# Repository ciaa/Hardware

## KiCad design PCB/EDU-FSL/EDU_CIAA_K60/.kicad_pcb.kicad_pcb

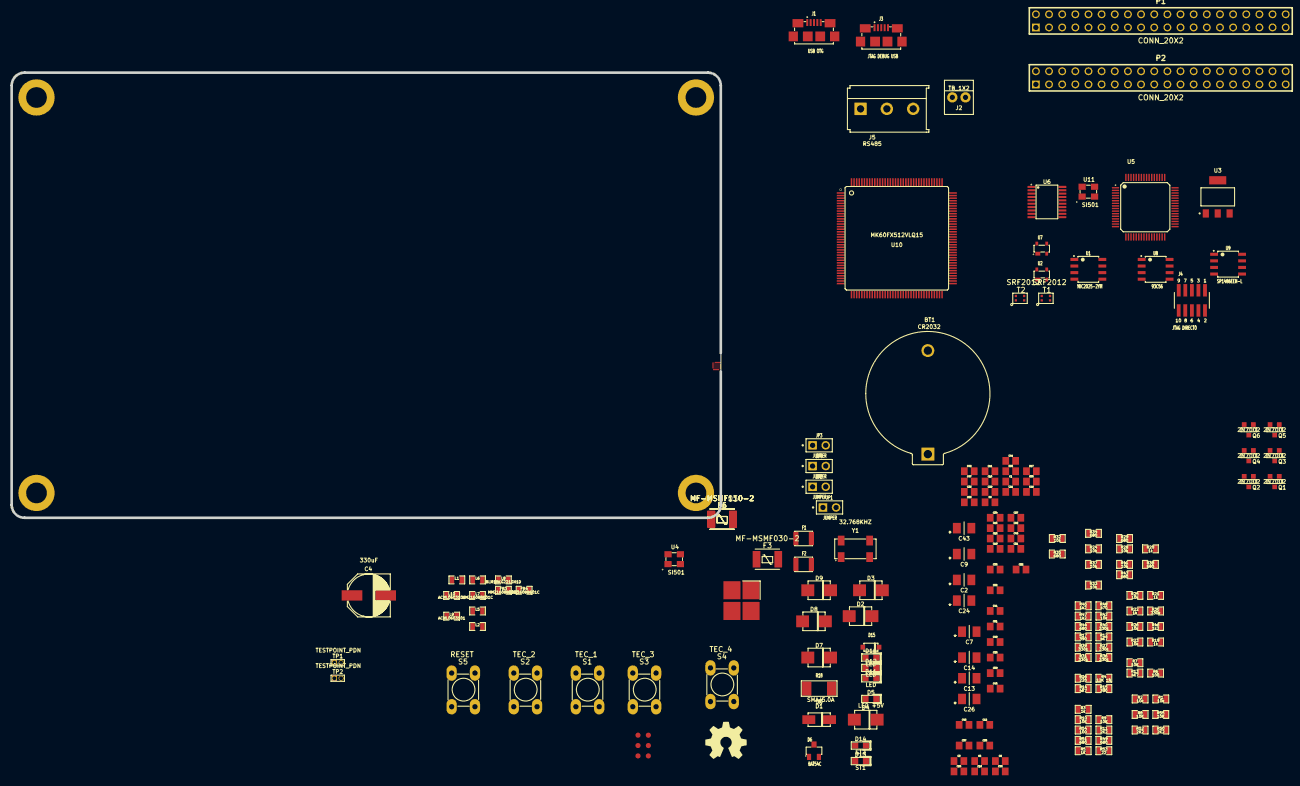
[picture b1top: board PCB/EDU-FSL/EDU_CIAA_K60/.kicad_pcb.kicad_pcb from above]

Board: 2 copper layers, 137.0 x 86.0 mm, 188 parts (0 on the bottom side), 164 nets, no tracks yet.

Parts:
BT1: CR2032; 2032batPTH
C1, C3, C5, C6, C8, C10, C11, C12, C15, C16, C17, C18, C19, C20, C21, C22, C23, C25, C27, C28, C29, C30, C31, C33, C34, C35, C37, C38, C39, C40, C41, C42, C44, C45, C48, C49, C50: 100nF; c_0805
C2, C9, C13, C14, C24: 4,7uF; c_1206POL
C4: 330uF; c_elec_8x10
C7, C26, C43: 10uF; c_1206POL
C32, C36: 18pF; c_0805
C46: 2.2uF; c_0805
C47, C51: 10nF; c_0805
D1: SMAJ5.0A; DO-214AC_SMA
D2, D3, D4: MBRS130LT3G; DO-214AA_SMB
D5: LED +5V; LED-0805
D6: BAT54C; SOT-23
D7, D8, D9: P6SMB12CAT3G; DO-214AA_SMB
D10, D11, D12: LED; LED-0805
D13: ST1; LED-0805
D14: ST2; LED-0805
D15: LL4148; SOD-123
F1, F2: USMF020; ptc_1210
F3, F5: MF-MSMF030-2; MF-MSMF
F4, F6: MF-MSMF110-2; MF-MSMF
FB3, FB4: MMZ1608B601C; SM0805
FD1, FD2, FD3, FD4, FD5, FD6: FIDUCIAL; Fiducial_1mm
G2: OSHWA
J1: USB OTG; USB_MicroAB
J2: TB_1X2; Con_2P
J3: JTAG DEBUG USB; USB_MicroAB
J4: JTAG DIRECTO; PIN_ARRAY_5x2_1.27_SMD
J5: RS485; bornier3
JP1, JP2, JP3, JP4: JUMPER; PIN_ARRAY_2x1
L1, L2, L5, L6: SM0805
L7: MMZ1608B601C; SM0805
L8: BLM18KG221SN1D; SM0805
L9, L10: ACML0603101; SM0805
LED1: LED_ARBG; PLCC-4
MH1, MH2, MH3, MH4: PCB_HOLE
P1, P2: CONN_20X2; PIN_ARRAY_20X2
Q1, Q2, Q3, Q4, Q5, Q6: 2N7002; SOT23GDS
R1, R2: 10k; r_0805
R3: 1k; r_0805
R4: 12K 1%; r_0805
R5: 1K; r_0805
R6, R54: 100; r_0805
R7, R8, R9, R10, R55: 10K; r_0805
R11, R50, R52: 2K2; r_0805
R12, R13, R14: 4K7; r_0805
R15, R17: 390; r_0805
R16: 220; r_0805
R18: 100; r_2010
R19, R20, R21, R22: 1k; SM0805
R23, R24, R25, R26, R28, R32, R33, R37, R41, R42: 10k; SM0805
R27, R30, R31, R36, R39, R40: 330k; SM0805
R29, R34, R35, R38, R43, R44: 680; SM0805
R45, R46, R47: 1k2; SM0805
R48: 470; SM0805
R49, R51: 680; r_0805
R53: 22; r_0805
S1: TEC_1; PUSH_SWITCH_THT
S2: TEC_2; PUSH_SWITCH_THT
S3: TEC_3; PUSH_SWITCH_THT
S4: TEC_4; PUSH_SWITCH_THT
S5: RESET; PUSH_SWITCH_THT
T1, T2: SRF2012
TP1, TP2: TESTPOINT_PDN
U1: MIC2025-2YM; SOIC-8
U2, U7: PRTR5V0U2X; SOT-143-4
U3: NCP1117ST33T3G; SOT-223
U4, U11: SI501; SI501_C
U5: FT2232H; TQFP64
U6: 74HC244; TSSOP-20
U8: 93C56; SOIC-8
U9: SP1486EEN-L; SOIC-8
U10: MK60FX512VLQ15; LQFP144
Y1: 32.768KHZ; 4SOJ

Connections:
+3.3V: C7.1, C8.1, C18.1, C19.1, C20.1, C21.1, C22.1, C23.1, C33.1, C34.1, C35.1, C37.1, C38.1, C39.1, C40.1, C41.1, C42.1, C43.1, C49.1, D6.2, F3.2, F5.2, FB3.1, J4.1, L5.1, L6.1, R2.1, R5.1, R7.2, R8.1, R9.1, R10.1, R23.1, R24.1, R25.1, R26.1, R50.1, R52.1, R55.1, TP1.1, U3.2, U4.1, U4.4, U5.20, U5.31, U5.42, U5.50, U5.56, U6.20, U8.6, U8.8, U10.5, U10.16, U10.43, U10.56, U10.70, U10.94, U10.108, U10.122, U10.135, U11.1, U11.4
+3.3VADC: C50.1, C51.2, FB3.2, L9.2, P1.15, U10.31
+5V: C1.1, C4.1, C5.1, C26.1, C27.2, D2.2, D3.2, D4.2, D10.1, D11.1, D12.1, F4.2, F6.2, LED1.4, R3.1, R13.1, R15.1, TP2.1, U1.7, U3.3, U9.8
+USB_JTAG_1V8: C9.1, C10.1, C15.1, C16.1, C17.1, U5.12, U5.37, U5.49, U5.64
/CPU/AUX_UART_CTS/SPI_CLK: P2.20, U10.128
/CPU/AUX_UART_RTS/SPI_CS: P2.22, U10.127
/CPU/AUX_UART_RX/SPI_MISO: P2.18, U10.130
/CPU/AUX_UART_TX/SPI_MOSI: P2.21, U10.129
/CPU/CAN_RD: P1.27, U10.98
/CPU/CAN_STB: P1.28, U10.54
/CPU/CAN_TD: P1.29, U10.97
/CPU/ETH_RST: P2.13, U10.73
/CPU/ETH_RXER: P2.11, U10.55
/CPU/I2C_SCL: P1.19, R52.2, U10.137
/CPU/I2C_SDA: P1.17, R50.2, U10.138
/CPU/LED0_B: R27.1, R28.1, U10.111
/CPU/LED0_G: R30.1, R32.1, U10.110
/CPU/LED0_R: R36.1, R37.1, U10.109
/CPU/LED1: R39.1, R41.1, U10.112
/CPU/LED2: R31.1, R33.1, U10.113
/CPU/LED3: R40.1, R42.1, U10.114
/CPU/PULS_0: R19.1, U10.103
/CPU/PULS_1: R20.1, U10.104
/CPU/PULS_2: R21.1, U10.105
/CPU/PULS_3: R22.1, U10.106
/CPU/RESET: D15.2, J4.10, P1.3, U6.12
/CPU/RS232_CTS: P1.22, U10.90
/CPU/RS232_RTS: P1.23, U10.89
/CPU/RS232_RXD: P1.21, U10.91
/CPU/RS232_TXD: P1.25, U10.92
/CPU/RS485_DIR: JP1.2, R14.2, U9.3, U10.131
/CPU/RS485_RXD: R13.2, U9.1, U10.133
/CPU/RS485_TXD: U9.4, U10.136
/CPU/SD_CLK: P2.35, R53.2
/CPU/SD_CMD: P2.36, U10.4
/CPU/SD_DAT0: P2.31, U10.2
/CPU/SD_DAT1: P2.38, U10.1
/CPU/SD_DAT2: P2.33, U10.8
/CPU/SD_DAT3: P2.40, U10.7
/CPU/SD_POW: P2.29, U10.126
/CPU/TCK: J4.4, U6.18, U10.50
/CPU/TDI: J4.8, U6.16, U10.51
/CPU/TDO: J4.6, U6.15, U10.52
/CPU/TEC_COL0: P1.39, U10.115
/CPU/TEC_COL1: P1.31, U10.116
/CPU/TEC_COL2: P1.34, U10.117
/CPU/TEC_F0: P1.33, U10.60
/CPU/TEC_F1: P1.36, U10.61
/CPU/TEC_F2: P1.37, U10.62
/CPU/TEC_F3: P1.35, U10.63
/CPU/TMS: J4.2, U6.14, U10.53
/CPU/USB_DM: T1.3, U2.2, U10.20
/CPU/USB_DP: T1.2, U2.3, U10.19
/CPU/USB_ID: D1.2, J1.4, U10.123
/CPU/USB_JTAG_UART_RXD: U5.38, U10.12
/CPU/USB_JTAG_UART_TXD: U5.39, U10.11
/CPU/VBAT: C6.1, D6.3, U10.42
/CPU/VREFH: C45.1, C47.2, L9.1, U10.32
/CPU/VREFL: C44.2, C45.2, C47.1, L10.1, U10.33
/Fuente/USB_VBUS: C2.1, C3.1, D3.1, L1.1, U1.6, U1.8, U2.4, U10.22
/GPIO/ADC0_1: R47.1, U10.77
/GPIO/ADC0_2: R46.1, U10.78
/GPIO/ADC0_3: R45.1, U10.79
/GPIO/DAC: R48.1, U10.38
/GPIO/ENET_CRS_DV: P2.10, U10.66
/GPIO/ENET_MDC: P2.8, U10.82
/GPIO/ENET_MDIO: P2.12, U10.81
/GPIO/ENET_REF_CLK: P2.15, U10.72
/GPIO/ENET_RXD0: P2.9, U10.65
/GPIO/ENET_RXD1: P2.4, U10.64
/GPIO/ENET_TXD0: P2.14, U10.68
/GPIO/ENET_TXD1: P2.16, U10.69
/GPIO/ENET_TX_EN: P2.6, U10.67
/GPIO/LCD1: P2.34, U10.141
/GPIO/LCD2: P2.32, U10.142
/GPIO/LCD3: P2.30, U10.143
/GPIO/LCD4: P2.26, U10.144
/GPIO/LCD_EN: P2.24, U10.139
/GPIO/LCD_RS: P2.28, U10.140
/JTAG/CHS_DBG: J3.6, J3.7, J3.8, J3.9, L7.2, U7.1
/JTAG/EECLK: R9.2, U5.62, U8.2
/JTAG/EECS: R8.2, U5.63, U8.1
/JTAG/EEDATA: R11.1, U5.61, U8.3
/JTAG/FT_OE: R7.1, U5.28, U6.1
/JTAG/FT_RST: U5.27, U6.8
/JTAG/FT_TCK: U5.16, U6.2
/JTAG/FT_TDI: U5.17, U6.4
/JTAG/FT_TDO: U5.18, U6.5
/JTAG/FT_TMS: U5.19, U6.6
/JTAG/USB_DEBUG_VBUS: C24.1, C25.1, D4.1, L8.2
/JTAG/USB_JTAG_DM: T2.3, U5.7, U7.3
/JTAG/USB_JTAG_DP: T2.2, U5.8, U7.2
/USB OTG/CHS_OTG: D1.1, J1.6, J1.7, J1.8, J1.9, L2.2, U2.1
/USB OTG/USB0_PPWR: R1.2, U1.1, U10.125
/USB OTG/USB0_PWR_FAULT: R2.2, U1.2, U10.124
/USB OTG/USB_DM_OTG: J1.2, T1.4
/USB OTG/USB_DP_OTG: J1.3, T1.1
GND: BT1.2, C1.2, C2.2, C3.2, C4.2, C5.2, C6.2, C7.2, C8.2, C9.2, C10.2, C11.2, C12.2, C13.2, C14.2, C15.2, C16.2, C17.2, C18.2, C19.2, C20.2, C21.2, C22.2, C23.2, C24.2, C25.2, C26.2, C27.1, C28.2, C29.2, C30.2, C31.2, C32.2, C33.2, C34.2, C35.2, C36.2, C37.2, C38.2, C39.2, C40.2, C41.2, C42.2, C43.2, C46.2, C48.1, C49.2, D5.2, D7.2, D9.2, D13.2, D14.2, FB4.1, J1.5, J2.2, J3.5, J4.3, J4.5, J4.9, L2.1, L7.1, MH1.1, MH2.1, MH3.1, MH4.1, P1.4, P1.18, P1.20, P1.24, P1.26, P1.30, P1.32, P1.38, P1.40, P2.3, P2.5, P2.7, P2.17, P2.19, P2.23, P2.25, P2.27, P2.37, P2.39, Q1.S, Q2.S, Q3.S, Q4.S, Q5.S, Q6.S, R1.1, R4.1, R12.1, R14.1, R17.2, R18.2, R27.2, R30.2, R31.2, R36.2, R39.2, R40.2, S1.2, S2.2, S3.2, S4.2, S5.2, TP1.2, TP2.2, U1.3, U3.1, U4.2, U5.1, U5.5, U5.10, U5.11, U5.13, U5.15, U5.25, U5.35, U5.47, U5.51, U6.10, U6.11, U6.13, U6.17, U6.19, U8.5, U9.5, U10.6, U10.17, U10.18, U10.44, U10.57, U10.71, U10.93, U10.107, U10.121, U10.134, U11.2, Y1.2, Y1.4
GNDA: C50.2, C51.1, FB4.2, L10.2, P1.5, P1.6, P1.8, P1.10, P1.12, P1.14, P1.16, U10.34
unnamed: R54.1, U10.45
unnamed: C48.2, D15.1, R55.2, S5.1, U10.74
unnamed: R51.2, U10.59
unnamed: C44.1, U10.37
unnamed: C46.1, U10.21
unnamed: R53.1, U10.3
unnamed: C36.1, U10.40, Y1.1
unnamed: R49.2, U10.58
unnamed: D14.1, R51.1
unnamed: D13.1, R49.1
unnamed: R54.2, U11.3
unnamed: C32.1, U10.41, Y1.3
unnamed: JP3.1, R16.1
unnamed: F1.2, J5.1
unnamed: D7.1, D8.1, F1.1, JP2.2, JP3.2, U9.6
unnamed: D8.2, D9.1, F2.1, JP4.2, R16.2, U9.7
unnamed: F2.2, J5.2
unnamed: JP2.1, R15.2
unnamed: JP4.1, R17.1
unnamed: J5.3, R18.1
unnamed: JP1.1, R12.2, U9.2
unnamed: D5.1, R3.2
unnamed: D2.1, J2.1
unnamed: BT1.1, D6.1
unnamed: J1.1, L1.2
unnamed: R10.2, R11.2, U8.4
unnamed: C12.1, C14.1, L5.2, U5.9
unnamed: J3.1, L8.1, U7.4
unnamed: C11.1, C13.1, L6.2, U5.4
unnamed: R6.2, U5.2
unnamed: R4.2, U5.6
unnamed: R5.2, U5.14
unnamed: J3.3, T2.1
unnamed: J3.2, T2.4
unnamed: R6.1, U4.3
unnamed: Q3.G, R33.2
unnamed: Q4.D, R38.2
unnamed: Q4.G, R37.2
unnamed: D10.2, R35.1
unnamed: Q3.D, R35.2
unnamed: LED1.2, R38.1
unnamed: Q1.D, R29.2
unnamed: D12.2, R44.1
unnamed: LED1.1, R29.1
unnamed: Q1.G, R28.2
unnamed: Q2.D, R34.2
unnamed: Q2.G, R32.2
unnamed: LED1.3, R34.1
unnamed: Q6.G, R42.2
unnamed: Q6.D, R44.2
unnamed: C29.1, R20.2, R24.2, S2.1
unnamed: C28.1, R19.2, R23.2, S1.1
unnamed: Q5.G, R41.2
unnamed: D11.2, R43.1
unnamed: Q5.D, R43.2
unnamed: C30.1, R21.2, R25.2, S3.1
unnamed: C31.1, R22.2, R26.2, S4.1
unnamed: P1.11, R47.2
unnamed: P1.9, R46.2
unnamed: P1.13, R48.2
unnamed: P1.7, R45.2
unnamed: F5.1, P2.1
unnamed: F6.1, P2.2
unnamed: F4.1, P1.2
unnamed: F3.1, P1.1

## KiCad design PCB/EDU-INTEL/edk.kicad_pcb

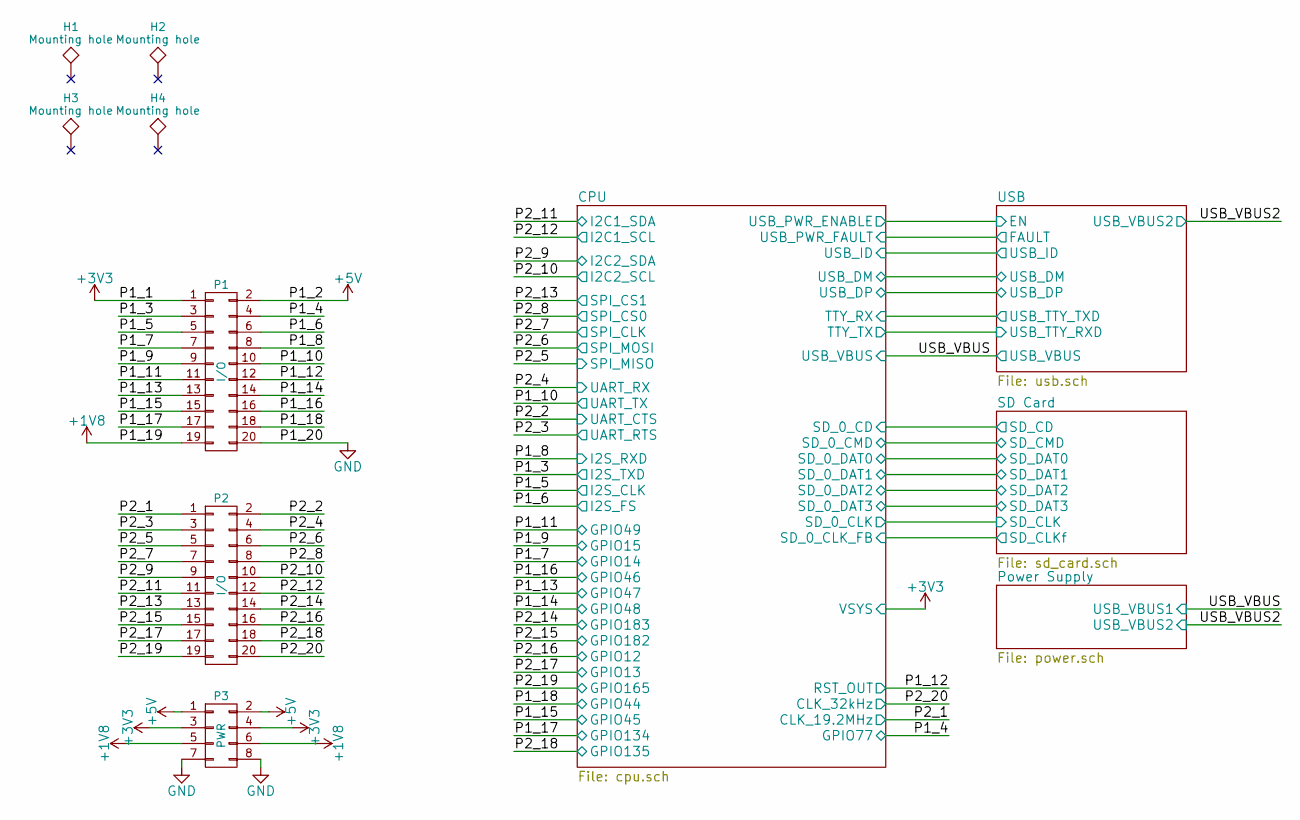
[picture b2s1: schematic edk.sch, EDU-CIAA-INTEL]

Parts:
H1, H2, H3, H4: Mounting hole; MountingHole_3mm
P1, P2: I/O; Pin_Header_Straight_2x10
P3: PWR; Pin_Header_Straight_2x04

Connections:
+1V8: P1.19, P3.5, P3.6; also elsewhere on the board
+3V3: P1.1, P3.3, P3.4; also elsewhere on the board
+5V: P1.2, P3.1, P3.2; also elsewhere on the board
/CPU/CLK_19.2MHz: P2.1; also elsewhere on the board
/CPU/CLK_32kHz: P2.20; also elsewhere on the board
/CPU/GPIO12: P2.16; also elsewhere on the board
/CPU/GPIO13: P2.17; also elsewhere on the board
/CPU/GPIO14: P1.7; also elsewhere on the board
/CPU/GPIO15: P1.9; also elsewhere on the board
/CPU/GPIO44: P1.18; also elsewhere on the board
/CPU/GPIO45: P1.15; also elsewhere on the board
/CPU/GPIO46: P1.16; also elsewhere on the board
/CPU/GPIO47: P1.13; also elsewhere on the board
/CPU/GPIO48: P1.14; also elsewhere on the board
/CPU/GPIO49: P1.11; also elsewhere on the board
/CPU/GPIO77: P1.4; also elsewhere on the board
/CPU/GPIO134: P1.17; also elsewhere on the board
/CPU/GPIO135: P2.18; also elsewhere on the board
/CPU/GPIO165: P2.19; also elsewhere on the board
/CPU/GPIO182: P2.15; also elsewhere on the board
/CPU/GPIO183: P2.14; also elsewhere on the board
/CPU/I2C1_SCL: P2.12; also elsewhere on the board
/CPU/I2C1_SDA: P2.11; also elsewhere on the board
/CPU/I2C2_SCL: P2.10; also elsewhere on the board
/CPU/I2C2_SDA: P2.9; also elsewhere on the board
/CPU/I2S_CLK: P1.5; also elsewhere on the board
/CPU/I2S_FS: P1.6; also elsewhere on the board
/CPU/I2S_RXD: P1.8; also elsewhere on the board
/CPU/I2S_TXD: P1.3; also elsewhere on the board
/CPU/RST_OUT: P1.12; also elsewhere on the board
/CPU/SPI_CLK: P2.7; also elsewhere on the board
/CPU/SPI_CS0: P2.8; also elsewhere on the board
/CPU/SPI_CS1: P2.13; also elsewhere on the board
/CPU/SPI_MISO: P2.5; also elsewhere on the board
/CPU/SPI_MOSI: P2.6; also elsewhere on the board
/CPU/UART_CTS: P2.2; also elsewhere on the board
/CPU/UART_RTS: P2.3; also elsewhere on the board
/CPU/UART_RX: P2.4; also elsewhere on the board
/CPU/UART_TX: P1.10; also elsewhere on the board
GND: P1.20, P3.7, P3.8; also elsewhere on the board

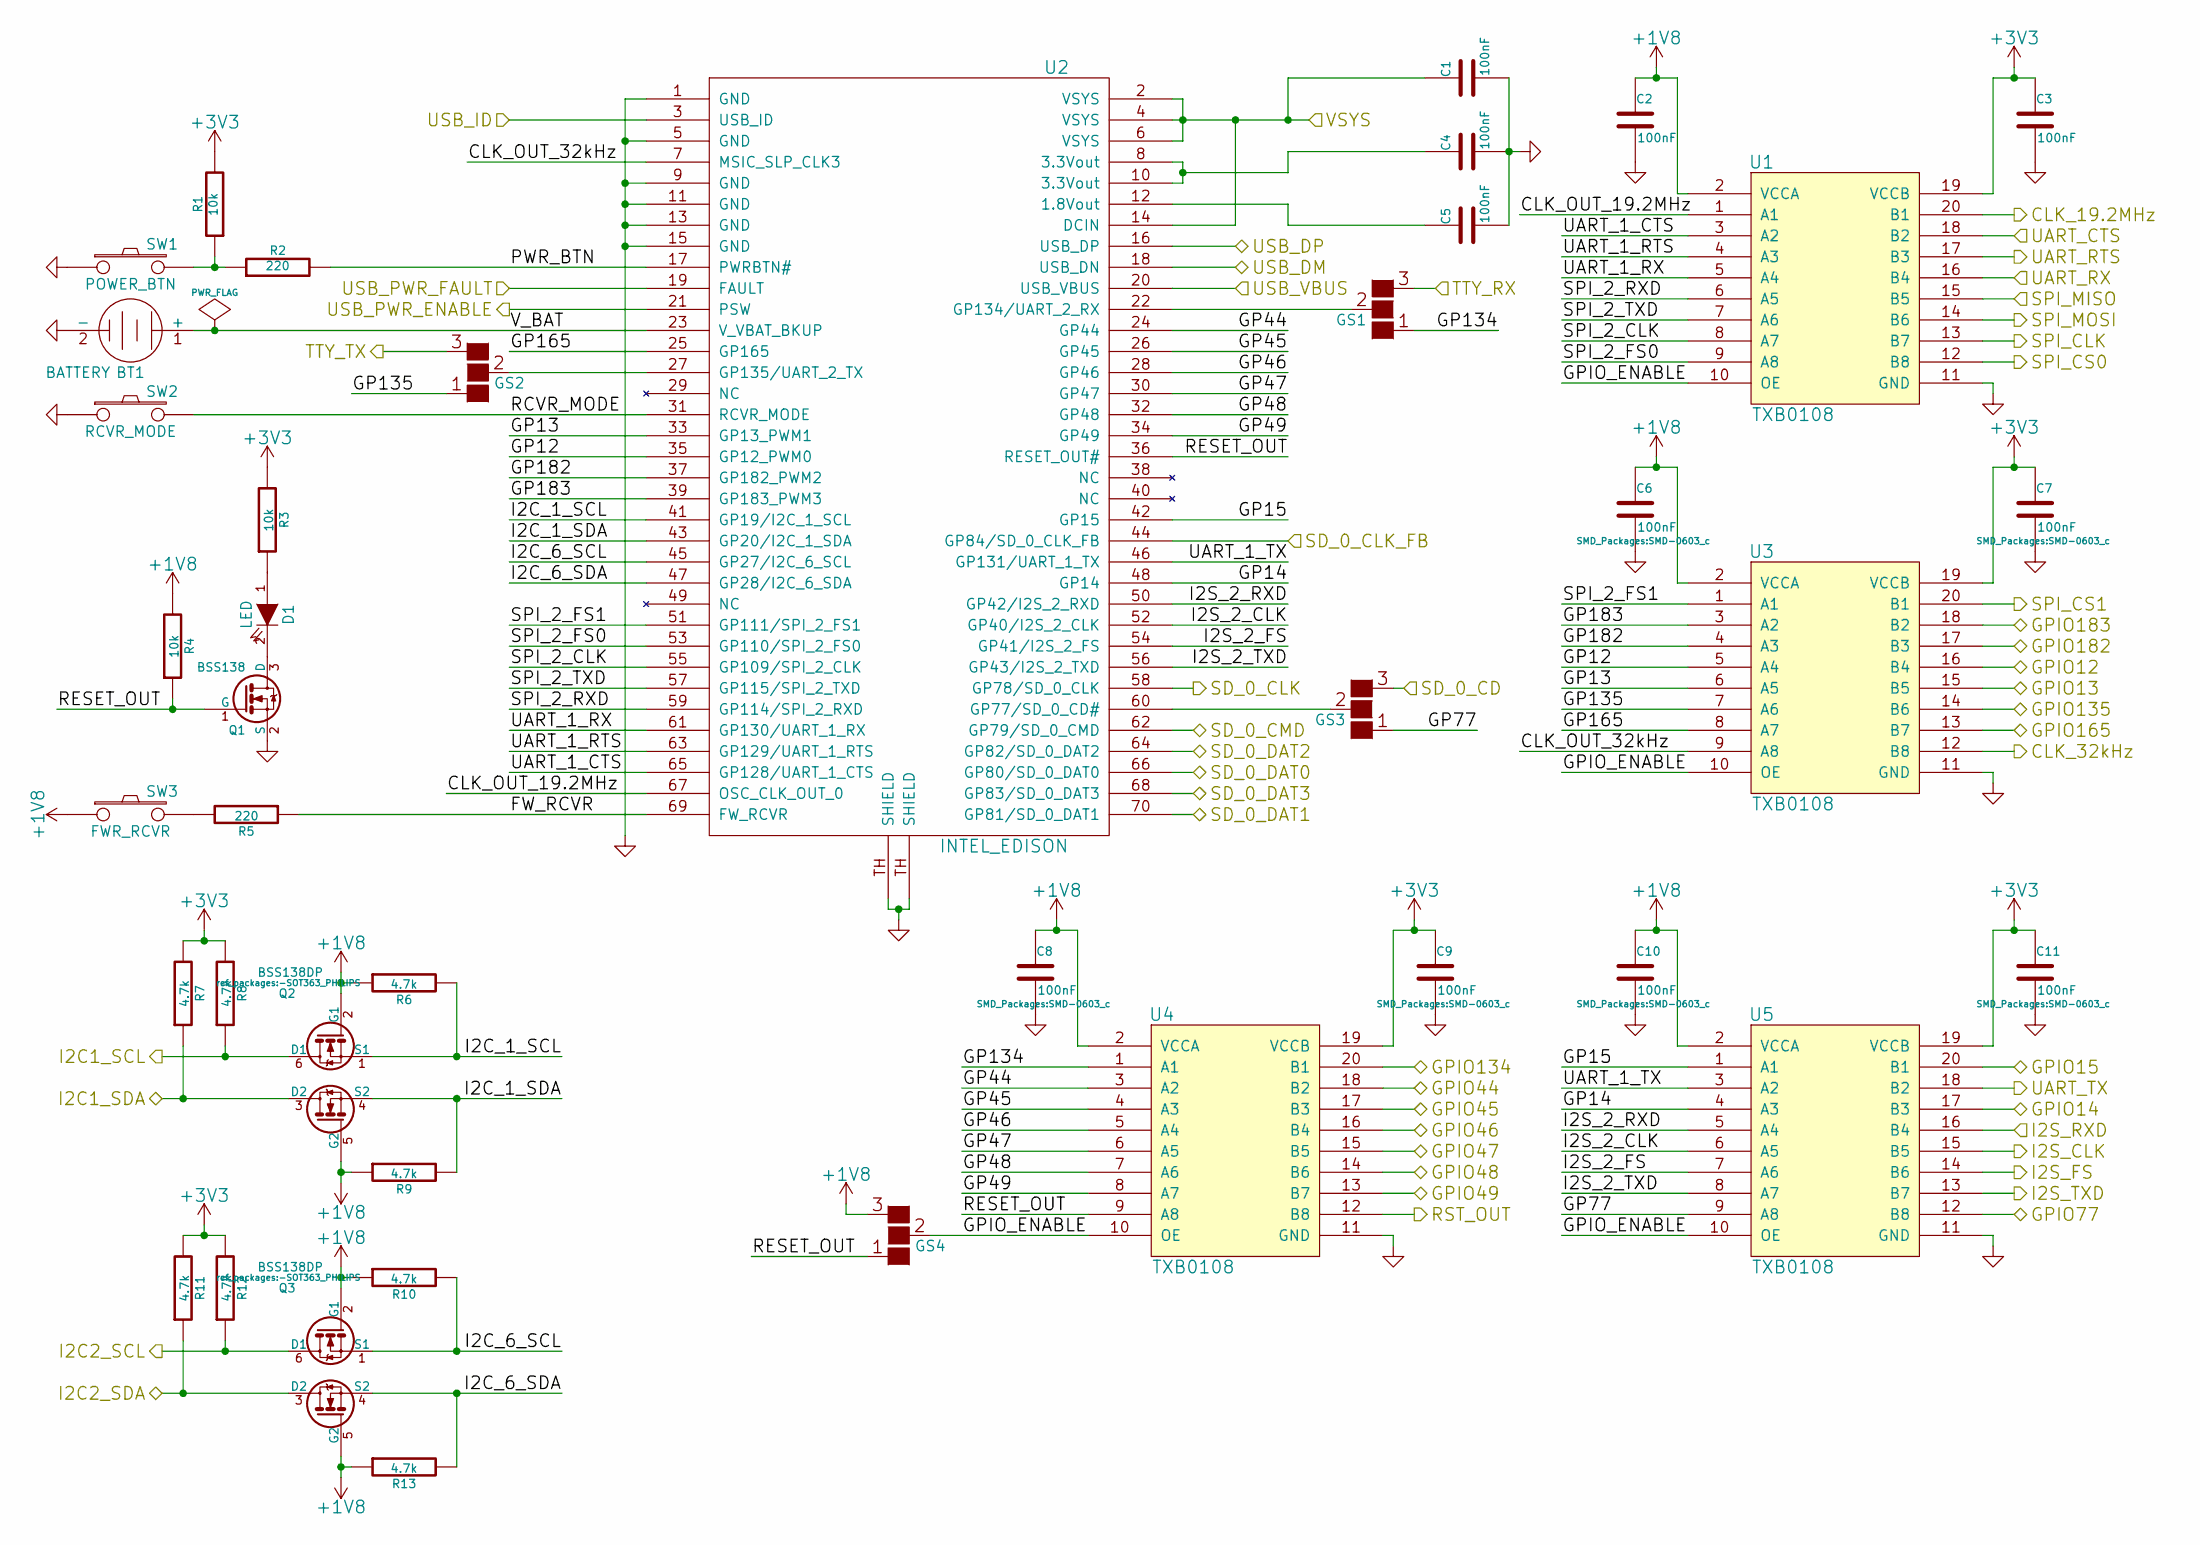
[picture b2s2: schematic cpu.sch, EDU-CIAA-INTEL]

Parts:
BT1: BATTERY; Pin_Header_Straight_1x02
C1, C2, C3, C4, C5, C6, C7, C8, C9, C10, C11: 100nF; SMD-0603_c
D1: LED; LED-0603
GS1, GS2, GS3, GS4: GS3
Q1: BSS138; SOT-23
Q2, Q3: BSS138DP; -SOT363_PHILIPS
R1, R3, R4: 10k; SMD-0603_r
R2, R5: 220; SMD-0603_r
R6, R7, R8, R9, R10, R11, R12, R13: 4.7k; SMD-0603_r
SW1: POWER_BTN; Pin_Header_Straight_1x02
SW2: RCVR_MODE; Pin_Header_Straight_1x02
SW3: FWR_RCVR; Pin_Header_Straight_1x02
U1, U3, U4, U5: TXB0108; SSOP-20_4.4x6.5mm_Pitch0.65mm
U2: INTEL_EDISON

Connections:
+1V8: C2.1, C6.1, C8.1, C10.1, GS4.3 (G3), Q2.2 (G1), Q2.5 (G2), Q3.2 (G1), Q3.5 (G2), R4.2, R6.1, R9.1, R10.1, R13.1, SW3.1, U1.2 (VCCA), U3.2 (VCCA), U4.2 (VCCA), U5.2 (VCCA); also elsewhere on the board
+3V3: C1.1, C3.1, C7.1, C9.1, C11.1, R1.2, R3.2, R7.2, R8.2, R11.2, R12.2, U1.19 (VCCB), U2.2 (VSYS), U2.4 (VSYS), U2.6 (VSYS), U2.14 (DCIN), U3.19 (VCCB), U4.19 (VCCB), U5.19 (VCCB); also elsewhere on the board
/CPU/CLK_19.2MHz: U1.20 (B1); also elsewhere on the board
/CPU/CLK_32kHz: U3.12 (B8); also elsewhere on the board
/CPU/CLK_OUT_19.2MHz: U1.1 (A1), U2.67 (OSC_CLK_OUT_0)
/CPU/CLK_OUT_32kHz: U2.7 (MSIC_SLP_CLK3), U3.9 (A8)
/CPU/FW_RCVR: R5.1, U2.69 (FW_RCVR)
/CPU/GP12: U2.35 (GP12_PWM0), U3.5 (A4)
/CPU/GP13: U2.33 (GP13_PWM1), U3.6 (A5)
/CPU/GP14: U2.48 (GP14), U5.4 (A3)
/CPU/GP15: U2.42 (GP15), U5.1 (A1)
/CPU/GP44: U2.24 (GP44), U4.3 (A2)
/CPU/GP45: U2.26 (GP45), U4.4 (A3)
/CPU/GP46: U2.28 (GP46), U4.5 (A4)
/CPU/GP47: U2.30 (GP47), U4.6 (A5)
/CPU/GP48: U2.32 (GP48), U4.7 (A6)
/CPU/GP49: U2.34 (GP49), U4.8 (A7)
/CPU/GP77: GS3.1 (G1), U5.9 (A8)
/CPU/GP134: GS1.1 (G1), U4.1 (A1)
/CPU/GP135: GS2.1 (G1), U3.7 (A6)
/CPU/GP165: U2.25 (GP165), U3.8 (A7)
/CPU/GP182: U2.37 (GP182_PWM2), U3.4 (A3)
/CPU/GP183: U2.39 (GP183_PWM3), U3.3 (A2)
/CPU/GPIO12: U3.16 (B4); also elsewhere on the board
/CPU/GPIO13: U3.15 (B5); also elsewhere on the board
/CPU/GPIO14: U5.17 (B3); also elsewhere on the board
/CPU/GPIO15: U5.20 (B1); also elsewhere on the board
/CPU/GPIO44: U4.18 (B2); also elsewhere on the board
/CPU/GPIO45: U4.17 (B3); also elsewhere on the board
/CPU/GPIO46: U4.16 (B4); also elsewhere on the board
/CPU/GPIO47: U4.15 (B5); also elsewhere on the board
/CPU/GPIO48: U4.14 (B6); also elsewhere on the board
/CPU/GPIO49: U4.13 (B7); also elsewhere on the board
/CPU/GPIO77: U5.12 (B8); also elsewhere on the board
/CPU/GPIO134: U4.20 (B1); also elsewhere on the board
/CPU/GPIO135: U3.14 (B6); also elsewhere on the board
/CPU/GPIO165: U3.13 (B7); also elsewhere on the board
/CPU/GPIO182: U3.17 (B3); also elsewhere on the board
/CPU/GPIO183: U3.18 (B2); also elsewhere on the board
/CPU/GPIO_ENABLE: GS4.2 (G2), U1.10 (OE), U3.10 (OE), U4.10 (OE), U5.10 (OE)
/CPU/I2C1_SCL: Q2.6 (D1), R8.1; also elsewhere on the board
/CPU/I2C1_SDA: Q2.3 (D2), R7.1; also elsewhere on the board
/CPU/I2C2_SCL: Q3.6 (D1), R12.1; also elsewhere on the board
/CPU/I2C2_SDA: Q3.3 (D2), R11.1; also elsewhere on the board
/CPU/I2C_1_SCL: Q2.1 (S1), R6.2, U2.41 (GP19/I2C_1_SCL)
/CPU/I2C_1_SDA: Q2.4 (S2), R9.2, U2.43 (GP20/I2C_1_SDA)
/CPU/I2C_6_SCL: Q3.1 (S1), R10.2, U2.45 (GP27/I2C_6_SCL)
/CPU/I2C_6_SDA: Q3.4 (S2), R13.2, U2.47 (GP28/I2C_6_SDA)
/CPU/I2S_2_CLK: U2.52 (GP40/I2S_2_CLK), U5.6 (A5)
/CPU/I2S_2_FS: U2.54 (GP41/I2S_2_FS), U5.7 (A6)
/CPU/I2S_2_RXD: U2.50 (GP42/I2S_2_RXD), U5.5 (A4)
/CPU/I2S_2_TXD: U2.56 (GP43/I2S_2_TXD), U5.8 (A7)
/CPU/I2S_CLK: U5.15 (B5); also elsewhere on the board
/CPU/I2S_FS: U5.14 (B6); also elsewhere on the board
/CPU/I2S_RXD: U5.16 (B4); also elsewhere on the board
/CPU/I2S_TXD: U5.13 (B7); also elsewhere on the board
/CPU/PWR_BTN: R2.2, U2.17 (PWRBTN#)
/CPU/RCVR_MODE: SW2.2, U2.31 (RCVR_MODE)
/CPU/RESET_OUT: GS4.1 (G1), Q1.1 (G), R4.1, U2.36 (RESET_OUT#), U4.9 (A8)
/CPU/RST_OUT: U4.12 (B8); also elsewhere on the board
/CPU/SD_0_CD: GS3.3 (G3); also elsewhere on the board
/CPU/SD_0_CLK: U2.58 (GP78/SD_0_CLK); also elsewhere on the board
/CPU/SD_0_CLK_FB: U2.44 (GP84/SD_0_CLK_FB); also elsewhere on the board
/CPU/SD_0_CMD: U2.62 (GP79/SD_0_CMD); also elsewhere on the board
/CPU/SD_0_DAT0: U2.66 (GP80/SD_0_DAT0); also elsewhere on the board
/CPU/SD_0_DAT1: U2.70 (GP81/SD_0_DAT1); also elsewhere on the board
/CPU/SD_0_DAT2: U2.64 (GP82/SD_0_DAT2); also elsewhere on the board
/CPU/SD_0_DAT3: U2.68 (GP83/SD_0_DAT3); also elsewhere on the board
/CPU/SPI_2_CLK: U1.8 (A7), U2.55 (GP109/SPI_2_CLK)
/CPU/SPI_2_FS0: U1.9 (A8), U2.53 (GP110/SPI_2_FS0)
/CPU/SPI_2_FS1: U2.51 (GP111/SPI_2_FS1), U3.1 (A1)
/CPU/SPI_2_RXD: U1.6 (A5), U2.59 (GP114/SPI_2_RXD)
/CPU/SPI_2_TXD: U1.7 (A6), U2.57 (GP115/SPI_2_TXD)
/CPU/SPI_CLK: U1.13 (B7); also elsewhere on the board
/CPU/SPI_CS0: U1.12 (B8); also elsewhere on the board
/CPU/SPI_CS1: U3.20 (B1); also elsewhere on the board
/CPU/SPI_MISO: U1.15 (B5); also elsewhere on the board
/CPU/SPI_MOSI: U1.14 (B6); also elsewhere on the board
/CPU/TTY_RX: GS1.3 (G3); also elsewhere on the board
/CPU/TTY_TX: GS2.3 (G3); also elsewhere on the board
/CPU/UART_1_CTS: U1.3 (A2), U2.65 (GP128/UART_1_CTS)
/CPU/UART_1_RTS: U1.4 (A3), U2.63 (GP129/UART_1_RTS)
/CPU/UART_1_RX: U1.5 (A4), U2.61 (GP130/UART_1_RX)
/CPU/UART_1_TX: U2.46 (GP131/UART_1_TX), U5.3 (A2)
/CPU/UART_CTS: U1.18 (B2); also elsewhere on the board
/CPU/UART_RTS: U1.17 (B3); also elsewhere on the board
/CPU/UART_RX: U1.16 (B4); also elsewhere on the board
/CPU/UART_TX: U5.18 (B2); also elsewhere on the board
/CPU/USB_DM: U2.18 (USB_DN); also elsewhere on the board
/CPU/USB_DP: U2.16 (USB_DP); also elsewhere on the board
/CPU/USB_ID: U2.3 (USB_ID); also elsewhere on the board
/CPU/USB_VBUS: U2.20 (USB_VBUS); also elsewhere on the board
/CPU/V_BAT: BT1.1 (+), U2.23 (V_VBAT_BKUP)
/USB/EN: U2.21 (PSW); also elsewhere on the board
/USB/FAULT: U2.19 (FAULT); also elsewhere on the board
GND: BT1.2 (-), C1.2, C2.2, C3.2, C4.2, C5.2, C6.2, C7.2, C8.2, C9.2, C10.2, C11.2, Q1.2 (S), SW1.1, SW2.1, U1.11 (GND), U2.1 (GND), U2.5 (GND), U2.9 (GND), U2.11 (GND), U2.13 (GND), U2.15 (GND), U2.TH (SHIELD), U3.11 (GND), U4.11 (GND), U5.11 (GND); also elsewhere on the board
unnamed: C4.1, U2.8 (3.3Vout), U2.10 (3.3Vout)
unnamed: C5.1, U2.12 (1.8Vout)
unnamed: D1.1 (A), R3.1
unnamed: D1.2 (K), Q1.3 (D)
unnamed: GS1.2 (G2), U2.22 (GP134/UART_2_RX)
unnamed: GS2.2 (G2), U2.27 (GP135/UART_2_TX)
unnamed: GS3.2 (G2), U2.60 (GP77/SD_0_CD#)
unnamed: R1.1, R2.1, SW1.2
unnamed: R5.2, SW3.2

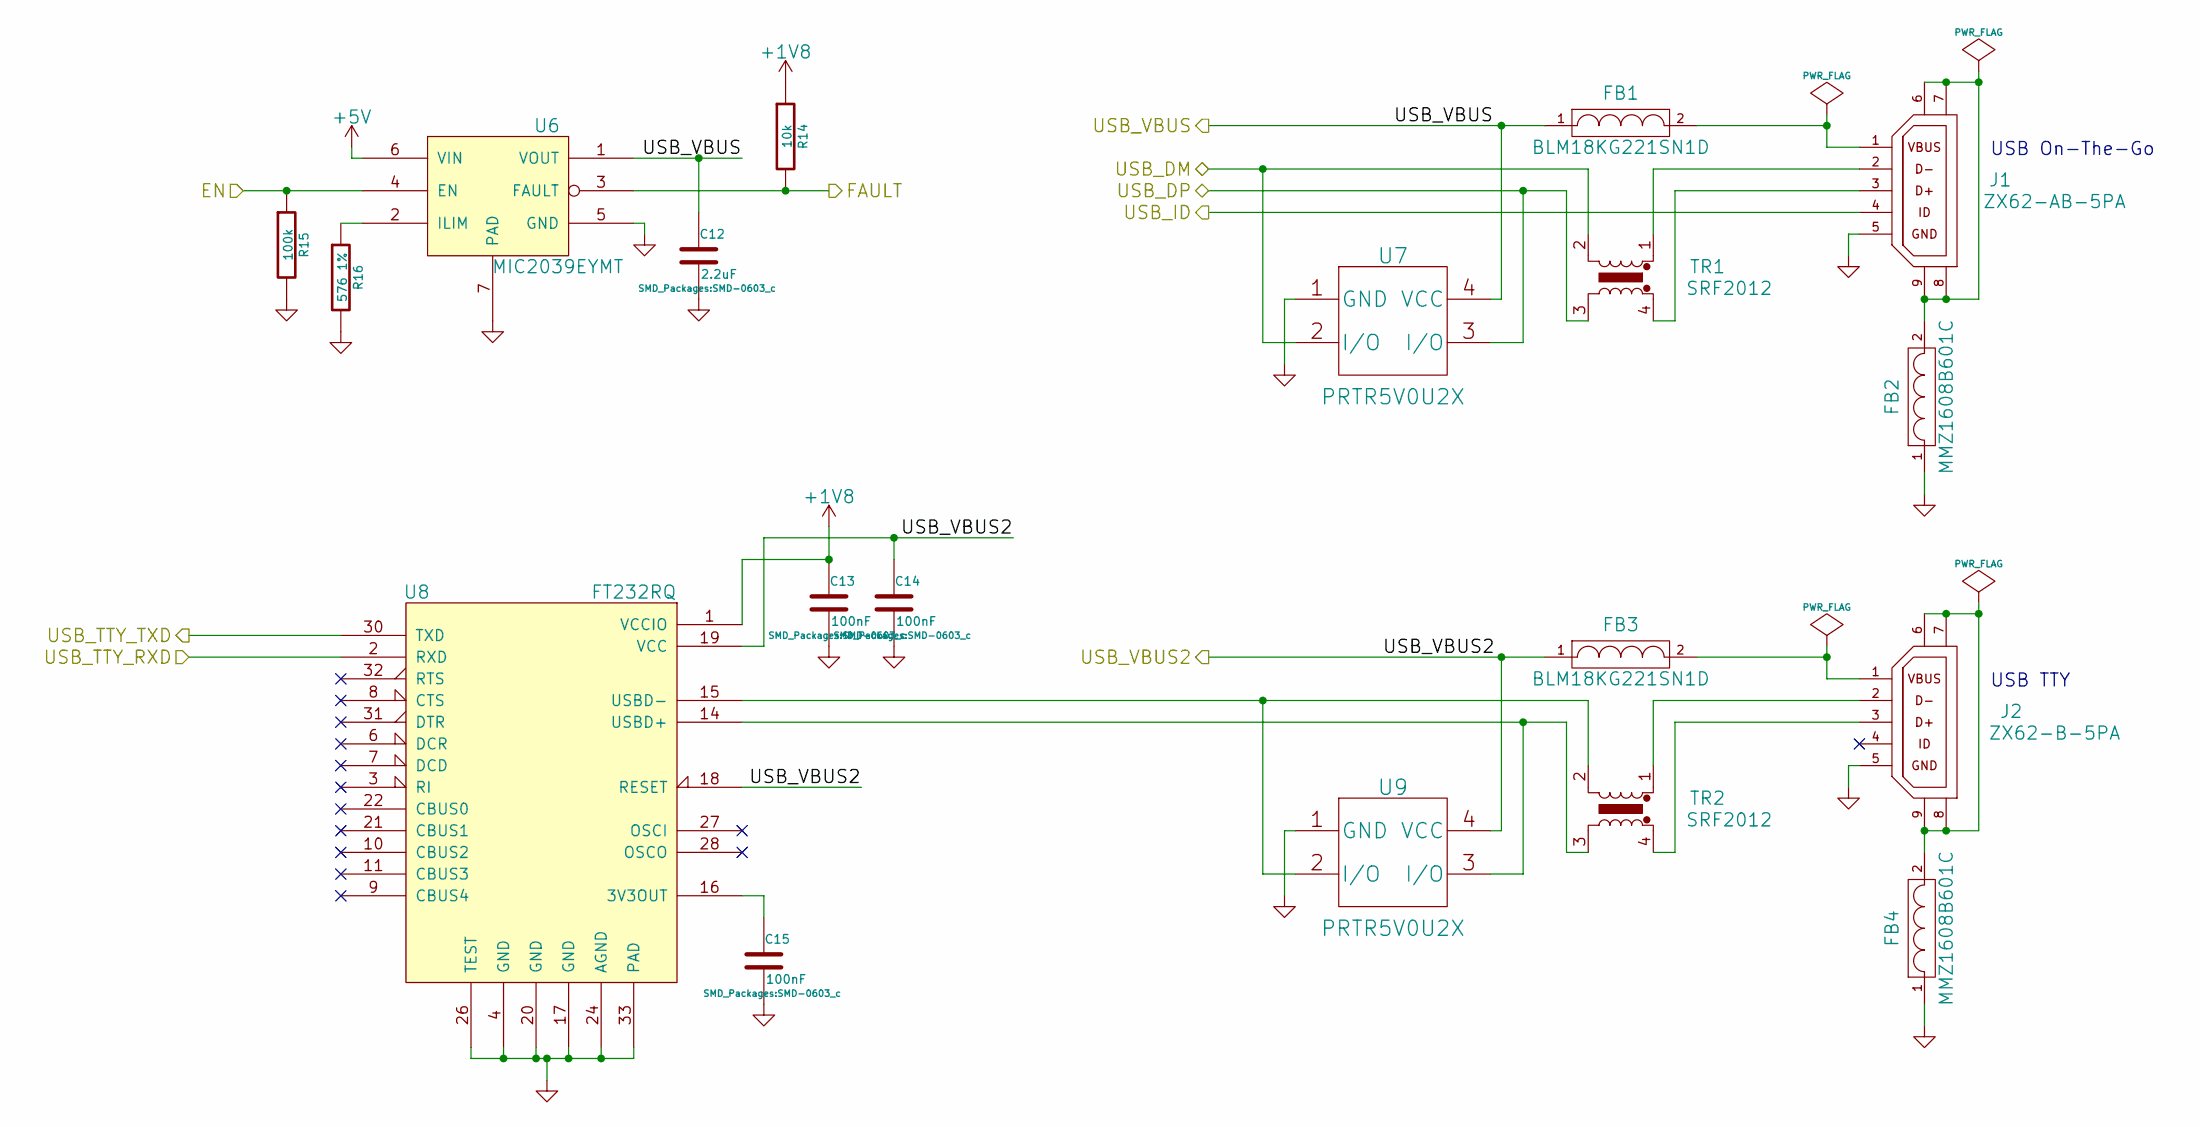
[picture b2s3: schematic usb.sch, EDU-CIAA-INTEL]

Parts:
C12: 2.2uF; SMD-0603_c
C13, C14, C15: 100nF; SMD-0603_c
FB1, FB3: BLM18KG221SN1D; SMD-0603
FB2, FB4: MMZ1608B601C; SMD-0603
J1: ZX62-AB-5PA; USB_microAB_ZX62-AB&B-5PA-11
J2: ZX62-B-5PA; USB_microAB_ZX62-AB&B-5PA-11
R14: 10k; SMD-0603_r
R15: 100k; SMD-0603_r
R16: 576 1%; SMD-0603_r
TR1, TR2: SRF2012
U6: MIC2039EYMT; DFN6_2x2mm_0.65Pitch
U7, U9: PRTR5V0U2X; SOT-143B
U8: FT232RQ; QFN-32-1EP

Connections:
+1V8: C13.1, R14.1, U8.1 (VCCIO); also elsewhere on the board
+5V: U6.6 (VIN); also elsewhere on the board
/CPU/TTY_RX: U8.30 (TXD); also elsewhere on the board
/CPU/TTY_TX: U8.2 (RXD); also elsewhere on the board
/CPU/USB_DM: TR1.2, U7.2 (I/O); also elsewhere on the board
/CPU/USB_DP: TR1.3, U7.3 (I/O); also elsewhere on the board
/CPU/USB_ID: J1.4 (USB_ID); also elsewhere on the board
/CPU/USB_VBUS: C12.1, FB1.1, U6.1 (VOUT), U7.4 (VCC); also elsewhere on the board
/Power Supply/USB_VBUS2: C14.1, FB3.1, U8.18 (RESET), U8.19 (VCC), U9.4 (VCC); also elsewhere on the board
/USB/EN: R15.1, U6.4 (EN); also elsewhere on the board
/USB/FAULT: R14.2, U6.3 (FAULT); also elsewhere on the board
GND: C12.2, C13.2, C14.2, C15.2, FB2.1, FB4.1, J1.5 (GND), J2.5 (GND), R15.2, R16.2, U6.5 (GND), U6.7 (PAD), U7.1 (GND), U8.4 (GND), U8.17 (GND), U8.20 (GND), U8.24 (AGND), U8.26 (TEST), U8.33 (PAD), U9.1 (GND); also elsewhere on the board
unnamed: C15.1, U8.16 (3V3OUT)
unnamed: FB1.2, J1.1 (VBUS)
unnamed: FB2.2, J1.6 (S2), J1.7 (S1), J1.8 (S3), J1.9 (S4)
unnamed: FB3.2, J2.1 (VBUS)
unnamed: FB4.2, J2.6 (S2), J2.7 (S1), J2.8 (S3), J2.9 (S4)
unnamed: J1.2 (USB_DN), TR1.1
unnamed: J1.3 (USB_DP), TR1.4
unnamed: J2.2 (USB_DN), TR2.1
unnamed: J2.3 (USB_DP), TR2.4
unnamed: R16.1, U6.2 (ILIM)
unnamed: TR2.2, U8.15 (USBD-), U9.2 (I/O)
unnamed: TR2.3, U8.14 (USBD+), U9.3 (I/O)

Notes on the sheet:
USB On-The-Go
USB TTY

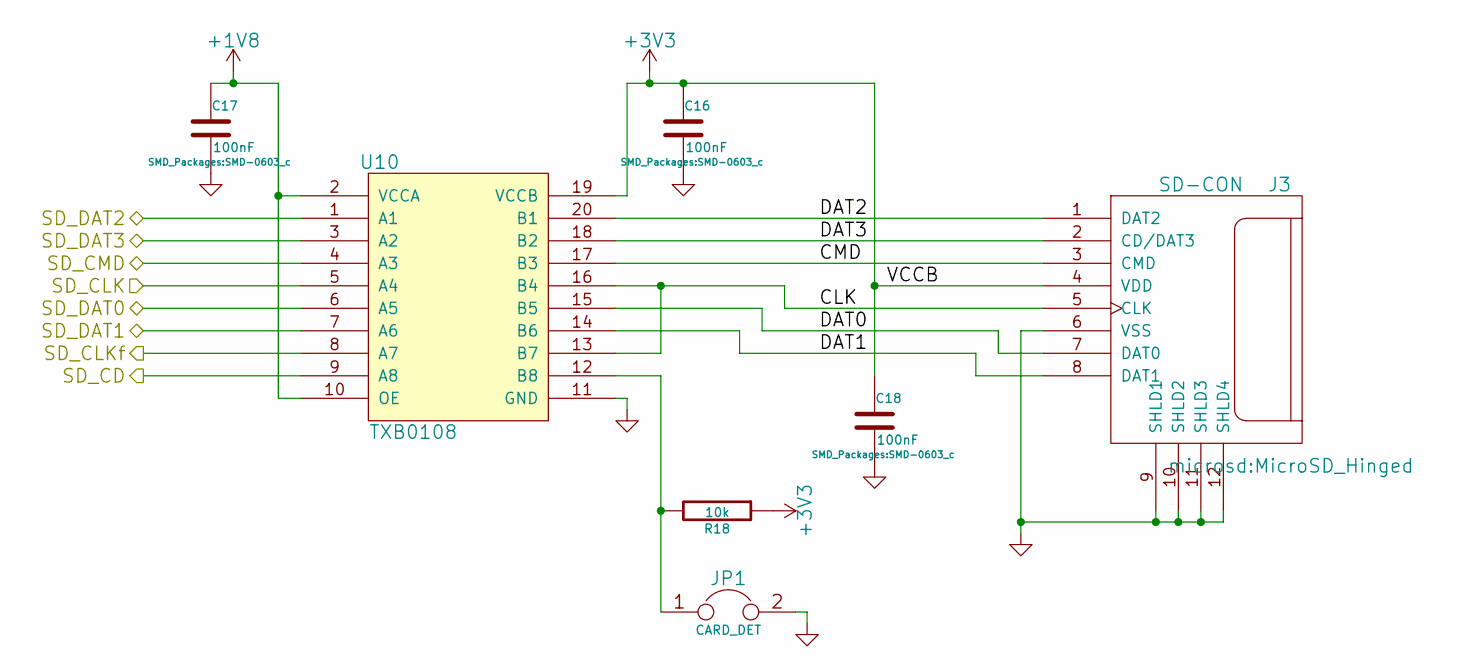
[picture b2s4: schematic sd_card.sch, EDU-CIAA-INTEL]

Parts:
C16, C17, C18: 100nF; SMD-0603_c
J3: SD-CON; MicroSD_Hinged
JP1: CARD_DET; Pin_Header_Straight_1x02
R18: 10k; SMD-0603_r
U10: TXB0108; SSOP-20_4.4x6.5mm_Pitch0.65mm

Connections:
+1V8: C17.1, U10.2 (VCCA), U10.10 (OE); also elsewhere on the board
+3V3: C16.1, C18.1, J3.4 (VDD), R18.1, U10.19 (VCCB); also elsewhere on the board
/CPU/SD_0_CD: U10.9 (A8); also elsewhere on the board
/CPU/SD_0_CLK: U10.5 (A4); also elsewhere on the board
/CPU/SD_0_CLK_FB: U10.8 (A7); also elsewhere on the board
/CPU/SD_0_CMD: U10.4 (A3); also elsewhere on the board
/CPU/SD_0_DAT0: U10.6 (A5); also elsewhere on the board
/CPU/SD_0_DAT1: U10.7 (A6); also elsewhere on the board
/CPU/SD_0_DAT2: U10.1 (A1); also elsewhere on the board
/CPU/SD_0_DAT3: U10.3 (A2); also elsewhere on the board
/SD Card/CLK: J3.5 (CLK), U10.13 (B7), U10.16 (B4)
/SD Card/CMD: J3.3 (CMD), U10.17 (B3)
/SD Card/DAT0: J3.7 (DAT0), U10.15 (B5)
/SD Card/DAT1: J3.8 (DAT1), U10.14 (B6)
/SD Card/DAT2: J3.1 (DAT2), U10.20 (B1)
/SD Card/DAT3: J3.2 (CD/DAT3), U10.18 (B2)
GND: C16.2, C17.2, C18.2, J3.6 (VSS), J3.9 (SHLD1), J3.10 (SHLD2), J3.11 (SHLD3), J3.12 (SHLD4), JP1.2, U10.11 (GND); also elsewhere on the board
unnamed: JP1.1, R18.2, U10.12 (B8)

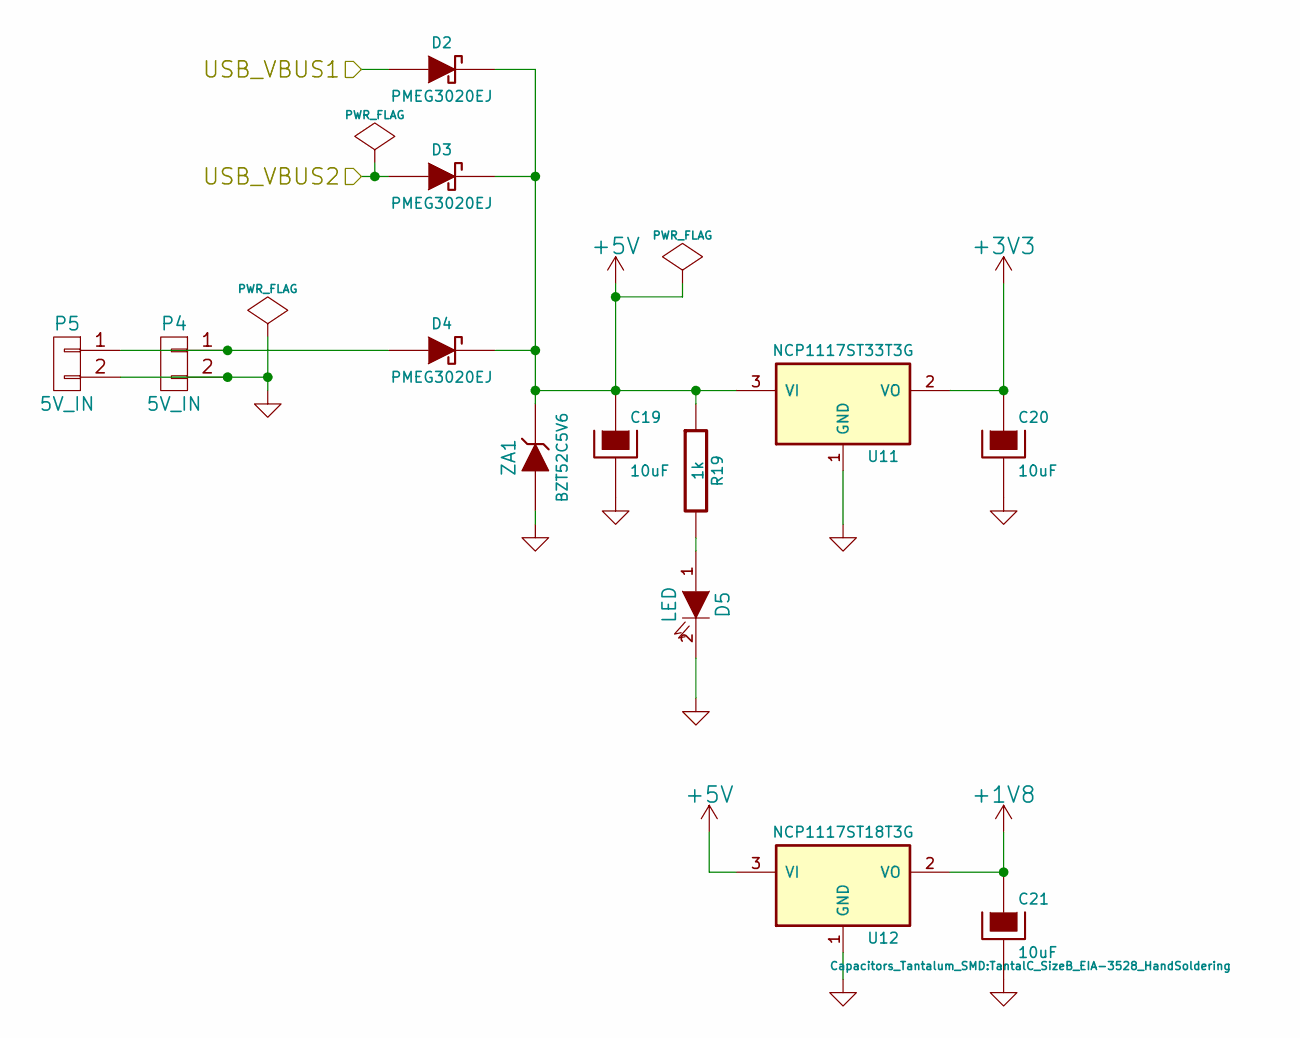
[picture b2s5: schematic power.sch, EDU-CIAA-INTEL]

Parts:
C19, C20, C21: 10uF; TantalC_SizeB_EIA-3528_HandSoldering
D2, D3, D4: PMEG3020EJ; SOD323
D5: LED; LED-0603
P4: 5V_IN; bornier2
P5: 5V_IN; Pin_Header_Straight_1x02
R19: 1k; SMD-0603_r
U11: NCP1117ST33T3G; SOT-223
U12: NCP1117ST18T3G; SOT-223
ZA1: BZT52C5V6; SOD123_INV

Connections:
+1V8: C21.1, U12.2 (VO); also elsewhere on the board
+3V3: C20.1, U11.2 (VO); also elsewhere on the board
+5V: C19.1, D2.2 (K), D3.2 (K), D4.2 (K), R19.1, U11.3 (VI), U12.3 (VI), ZA1.2 (K); also elsewhere on the board
/CPU/USB_VBUS: D2.1 (A); also elsewhere on the board
/Power Supply/USB_VBUS2: D3.1 (A); also elsewhere on the board
GND: C19.2, C20.2, C21.2, D5.2 (K), P4.2, P5.2, P5.3, U11.1 (GND), U12.1 (GND), ZA1.1 (A); also elsewhere on the board
unnamed: D4.1 (A), P4.1, P5.1
unnamed: D5.1 (A), R19.2
